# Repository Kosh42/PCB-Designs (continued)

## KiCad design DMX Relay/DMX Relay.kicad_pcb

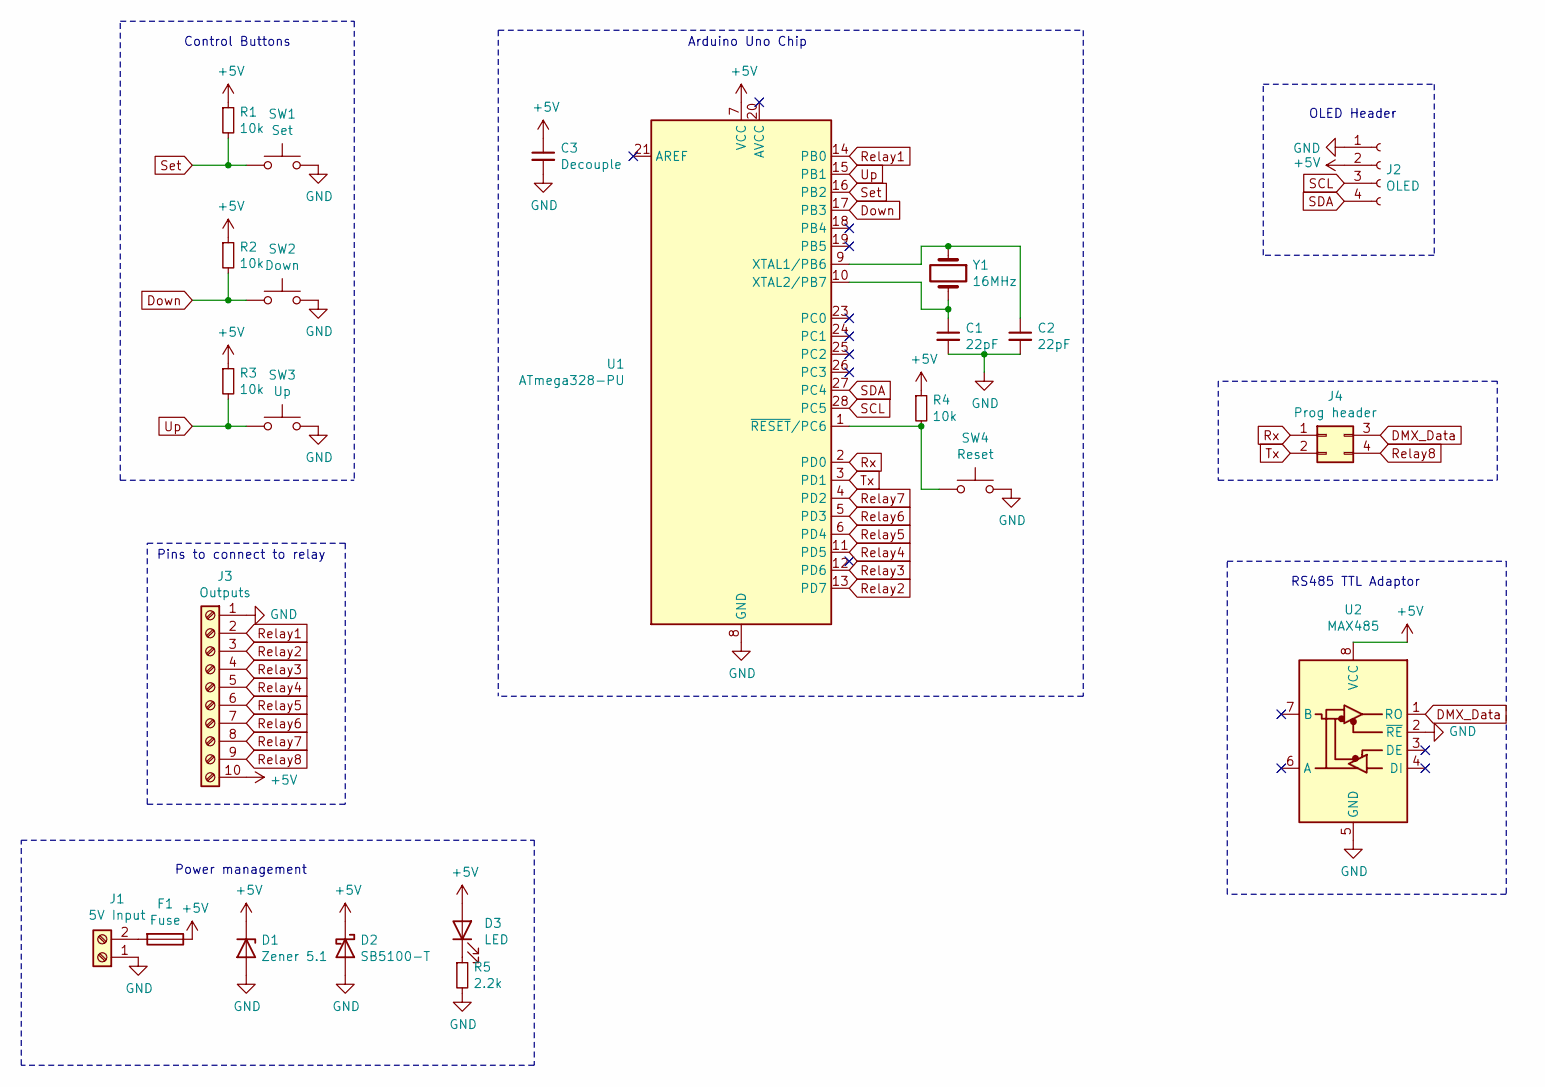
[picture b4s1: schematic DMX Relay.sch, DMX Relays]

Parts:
C1, C2: 22pF; C_Disc_D3.0mm_W1.6mm_P2.50mm
C3: Decouple; C_Disc_D3.0mm_W1.6mm_P2.50mm
D1: Zener 5.1; D_DO-15_P10.16mm_Horizontal
D2: SB5100-T; D_DO-27_P12.70mm_Horizontal
D3: LED; LED_D3.0mm
F1: Fuse; FUSE_3544-2
J1: 5V Input; TerminalBlock_bornier-2_P5.08mm
J2: OLED; PinSocket_1x04_P2.54mm_Vertical
J3: Outputs; TerminalBlock_Phoenix_MKDS-1,5-10-5.08_1x10_P5.08mm_Horizon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
J4: Prog header; PinHeader_2x02_P2.54mm_Vertical
R1, R2, R3, R4: 10k; R_Axial_DIN0207_L6.3mm_D2.5mm_P7.62mm_Horizontal
R5: 2.2k; R_Axial_DIN0207_L6.3mm_D2.5mm_P7.62mm_Horizontal
SW1: Set; SW_PUSH_6mm
SW2: Down; SW_PUSH_6mm
SW3: Up; SW_PUSH_6mm
SW4: Reset; SW_PUSH_6mm
U1: ATmega328-PU; DIP-28_W7.62mm
U2: MAX485; Max4852
Y1: 16MHz; Crystal_HC49-U_Vertical

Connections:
+5V: C3.1, D1.1 (K), D2.1 (K), D3.2 (A), F1.1, J2.2, J3.10, R1.1, R2.1, R3.1, R4.1, U1.7 (VCC), U2.8 (VCC)
DMX_Data: J4.3, U2.1 (RO)
Down: R2.2, SW2.1, U1.17 (PB3)
GND: C1.2, C2.2, C3.2, D1.2 (A), D2.2 (A), J1.1, J2.1, J3.1, R5.2, SW1.2, SW2.2, SW3.2, SW4.2, U1.8 (GND), U1.22 (GND), U2.2 (~RE), U2.5 (GND)
unnamed: C1.1, U1.10 (XTAL2/PB7), Y1.2
unnamed: C2.1, U1.9 (XTAL1/PB6), Y1.1
unnamed: D3.1 (K), R5.1
unnamed: F1.2, J1.2
unnamed: R4.2, SW4.1, U1.1 (~RESET~/PC6)
Relay1: J3.2, U1.14 (PB0)
Relay2: J3.3, U1.13 (PD7)
Relay3: J3.4, U1.12 (PD6)
Relay4: J3.5, U1.11 (PD5)
Relay5: J3.6, U1.6 (PD4)
Relay6: J3.7, U1.5 (PD3)
Relay7: J3.8, U1.4 (PD2)
Relay8: J3.9, J4.4
Rx: J4.1, U1.2 (PD0)
SCL: J2.3, U1.28 (PC5)
SDA: J2.4, U1.27 (PC4)
Set: R1.2, SW1.1, U1.16 (PB2)
Tx: J4.2, U1.3 (PD1)
Up: R3.2, SW3.1, U1.15 (PB1)

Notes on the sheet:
OLED Header
RS485 TTL Adaptor
Control Buttons
Arduino Uno Chip
Pins to connect to relay
Power management

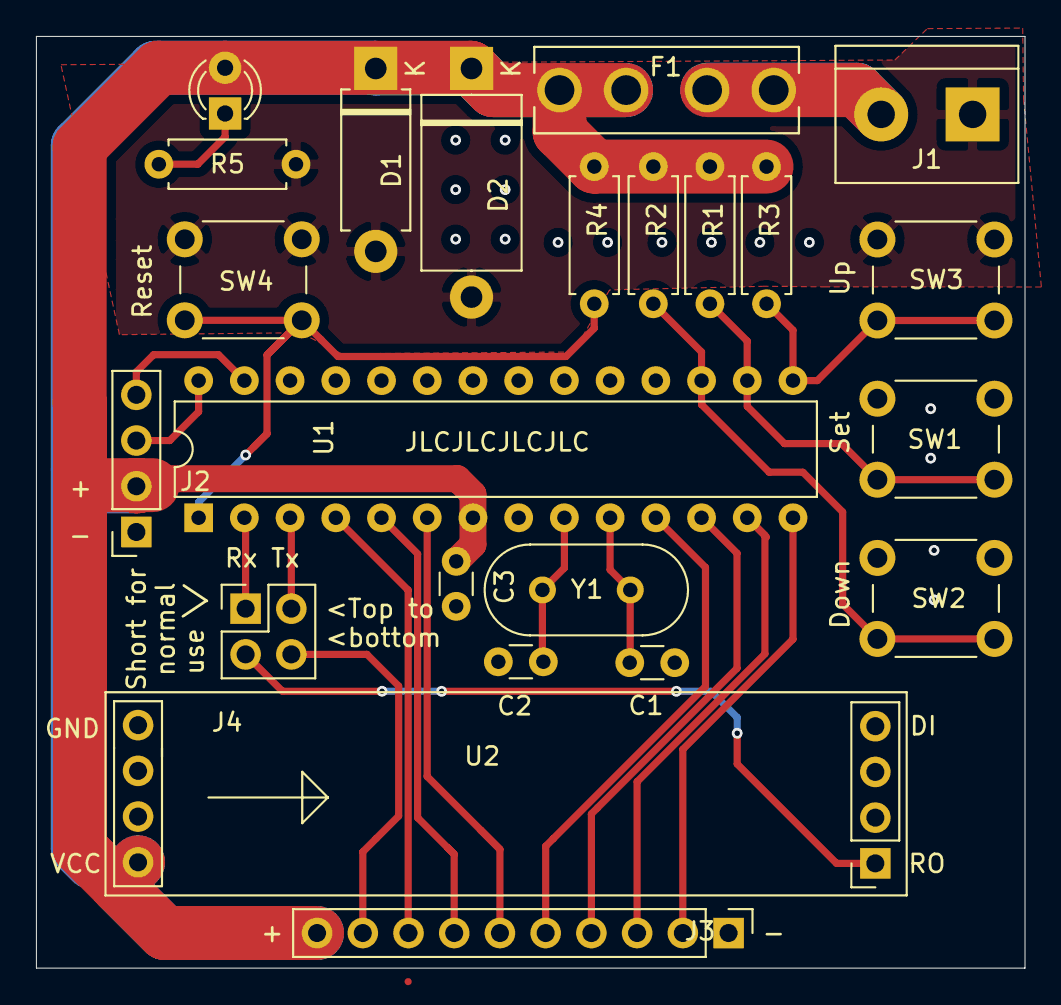
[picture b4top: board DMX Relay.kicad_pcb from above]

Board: 2 copper layers, 54.9 x 51.8 mm, 23 parts (0 on the bottom side), 23 nets.

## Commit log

2021-01-27 DOH!
2021-01-31 V0.3d
    Added decoupling caps to diff drivers, various tweaks, changed SMD footprints to allow 95% JLBPCB assembly. C part numbers added in to the BOM and JLC files generated with https://github.com/matthewl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
2021-01-31 DMX Relays
    Code based on https://github.com/markphelan/arduino
    My code with 8 relays and reconfigured buttons: https://github.com/Kosh42/arduino
2021-01-31 DMX to V0.2
    Added decoupling cap and abaility to replace Rx and Tx signals with a TTL to program in situ.
    And the code compiled and ran on the ATMega328P!
    https://github.com/Kosh42/arduino/tree/master/DMXrelay
2021-02-03 Screw terminal swap out
2021-03-13 Reorg Files And Bump T24 to V0.7
    V0.7 fixed DMX being driven from non-UART pins. JSON/Firmware still to write for this version.
2021-03-14 SD Bus & Plugs
    Fix GPIO and buttons sharing SD pins. Fix spacing on plugs as too tight.
2021-03-14 Bump to 0.7b
    Changed DMX connector. Tweaks.
2021-03-15 Bump Versions
2021-03-18 Inc Buck
2021-03-18 Revert "Inc Buck"
    This reverts commit dbd6f2490a180fa10e79e66cec7a5f8d0fb3866e.
2021-03-18 Correct Buck
    Connect buck ground to ground.
2021-03-18 0.7
    Buck and reroute
2021-04-13 Updates. T24 to 7e
2021-04-13 Generate 0.7e Gerber
2021-05-01 Add AB PCB
2021-05-16 KoshABTool
2021-07-05 3D files
2021-07-10 Clean Up
2021-11-17 Updates
    Add a few clean ups and upload settings JSON.
2023-10-20 add eeprom files
2023-10-20 file update
